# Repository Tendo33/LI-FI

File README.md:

# Li-Fi (Light Fidelity): Visible Light Communication Based on STM32

Innovative advancements in wireless communication have led to the development of Li-Fi, a technology that harnesses the power of visible light for data transmission. Li-Fi, or Light Fidelity, is a form of visible light communication (VLC) that uses light-emitting diodes (LEDs) as a medium for high-speed, bidirectional data transfer. This technology leverages the rapid switching capabilities of LEDs to transmit binary information, offering a new dimension to the realm of wireless networking.

At the heart of this cutting-edge system lies the STM32 microcontroller, a powerful and versatile device developed by STMicroelectronics. The STM32 family offers a wide range of performance, power consumption, and integration options, making it suitable for various applications, including complex high-end products and low-power devices. In the context of Li-Fi, the STM32 serves as the brain that controls the modulation and demodulation of light signals, enabling efficient and reliable data communication.

The STM32 microcontroller, with its robust processing capabilities, is capable of managing the intricate details of Li-Fi communication protocols. It can handle the modulation techniques required to encode digital data onto the light waves and decode them at the receiver end. Moreover, the STM32 can support additional functionalities such as error correction, signal processing, and security features, which are crucial for maintaining high data integrity and confidentiality in Li-Fi networks.

One of the significant advantages of using Li-Fi technology over traditional Wi-Fi is the potential for higher bandwidth and data rates. Since the visible light spectrum has a much wider bandwidth than radio frequencies, Li-Fi can theoretically achieve gigabit speeds. Additionally, Li-Fi can coexist harmoniously with existing wireless technologies without causing interference, making it a promising solution for densely populated areas or environments where radio frequency emissions are restricted, such as hospitals and aircraft cabins.

The integration of Li-Fi with the STM32 microcontroller opens up exciting possibilities for various industries. From enhancing the Internet of Things (IoT) ecosystem to improving connectivity in smart homes and offices, Li-Fi powered by STM32 can revolutionize the way we interact with our environment. With its ability to provide secure, high-speed connectivity using everyday lighting fixtures, Li-Fi stands as a beacon of innovation in the field of wireless communication.

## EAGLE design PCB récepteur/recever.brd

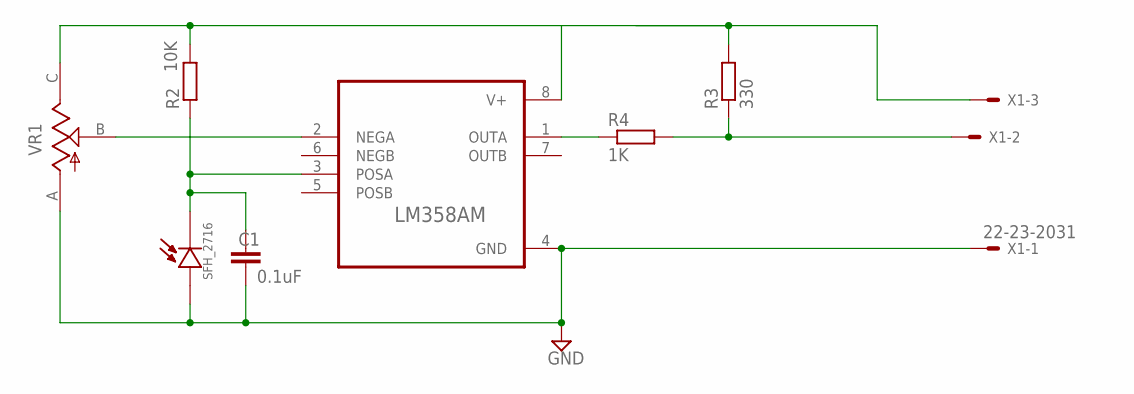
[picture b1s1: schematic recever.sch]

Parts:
C1: 0.1uF; C1206
D1: SFH_2716; LEDC2012X100N
R2: 10K; R1206
R3: 330; R1206
R4: 1K; R1206
U1: LM358AM; SOIC127P599X175-8N
VR1: 10K; TRIM_TS53YJ103MR10
X1: 22-23-2031

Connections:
GND: C1.2, D1.A, U1.4 (GND), VR1.A, X1.1
unnamed: R2.2, R3.2, U1.8 (V+), VR1.C, X1.3
unnamed: R3.1, R4.2, X1.2
unnamed: U1.2 (NEGA), VR1.B
unnamed: C1.1, D1.C, R2.1, U1.3 (POSA)
unnamed: R4.1, U1.1 (OUTA)

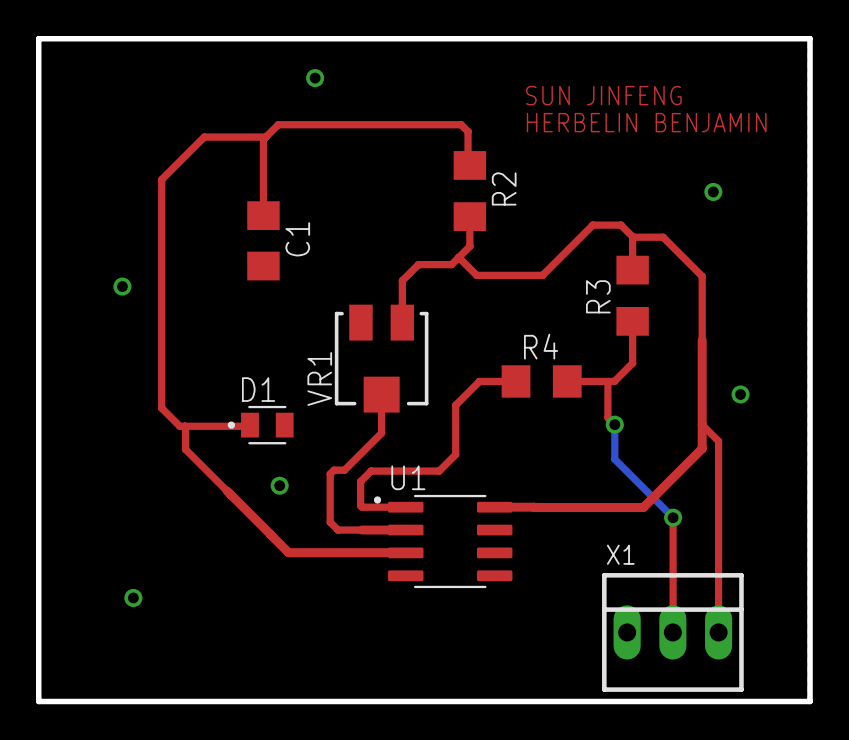
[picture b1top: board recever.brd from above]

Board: 2 copper layers, 42.9 x 36.8 mm, 8 parts (0 on the bottom side), 6 nets.

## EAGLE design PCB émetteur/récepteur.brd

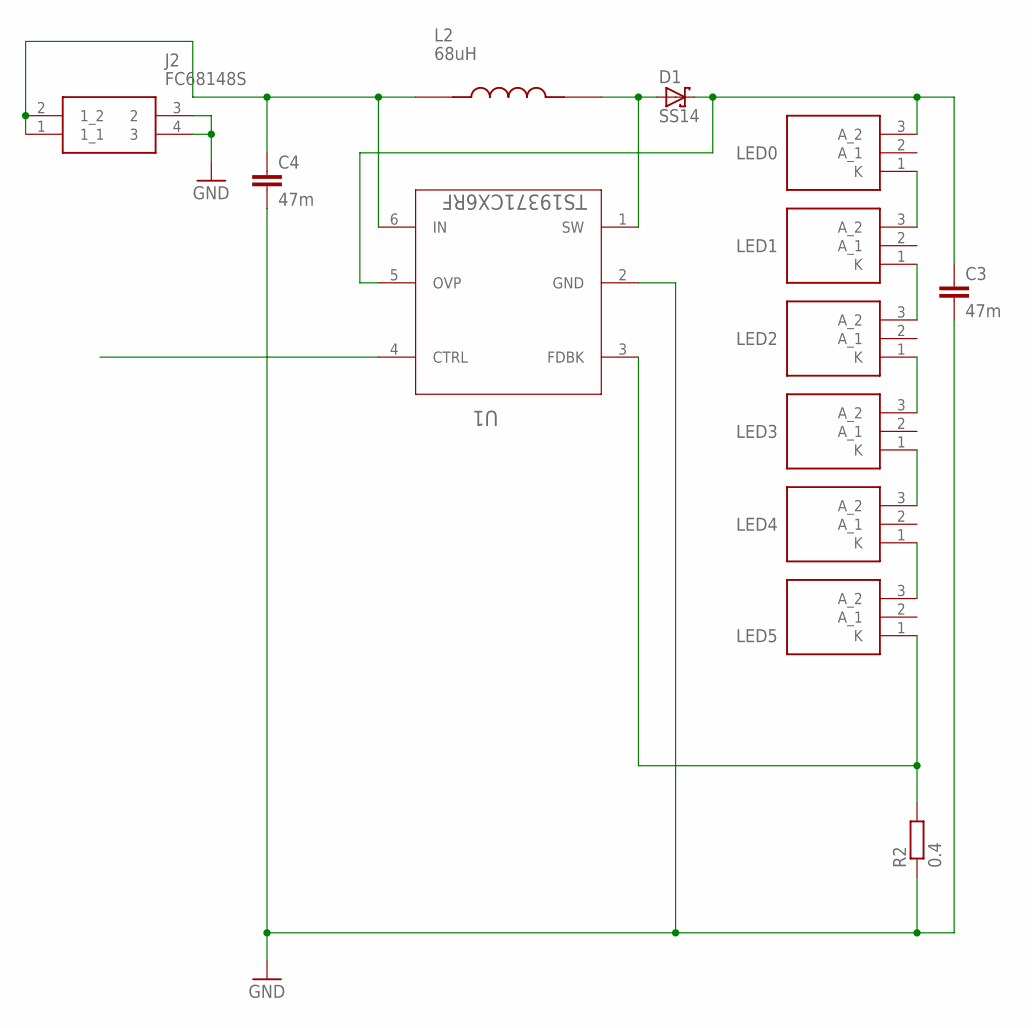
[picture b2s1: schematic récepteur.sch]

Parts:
C3, C4: 47m; C1206K
D1: SS14; DO-214AC
J2: FC68148S; FC68148S_2
L2: 68uH; IND_1255AY-680M=P3
LED0, LED1, LED2, LED3, LED4, LED5: LED-CREE-JK3030; JK3030AWT000000000A0HK230E
R2: 0.4; R1206
U1: TS19371CX6RF; SOT95P280X125-6N

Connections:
GND: C3.2, C4.2, J2.3 (2), J2.4 (3), R2.1, U1.2 (GND)
unnamed: LED0.1 (K), LED1.3 (A_2)
unnamed: LED1.1 (K), LED2.3 (A_2)
unnamed: LED2.1 (K), LED3.3 (A_2)
unnamed: LED3.1 (K), LED4.3 (A_2)
unnamed: LED4.1 (K), LED5.3 (A_2)
unnamed: LED5.1 (K), R2.2, U1.3 (FDBK)
unnamed: C4.1, J2.1 (1_1), J2.2 (1_2), L2.1, U1.6 (IN)
unnamed: D1.A, L2.2, U1.1 (SW)
unnamed: C3.1, D1.K, LED0.3 (A_2), U1.5 (OVP)

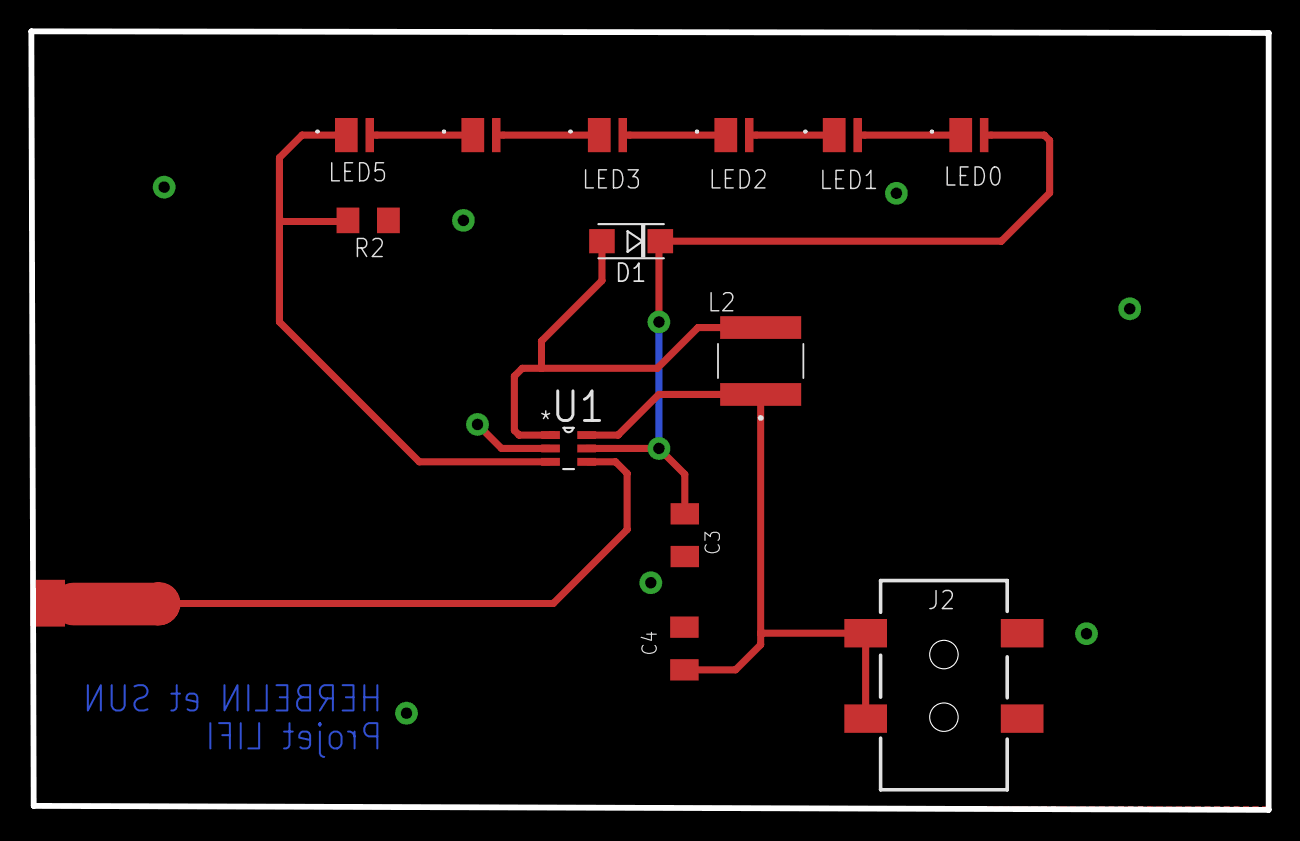
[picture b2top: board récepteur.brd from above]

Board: 2 copper layers, 87.0 x 54.7 mm, 13 parts (0 on the bottom side), 10 nets.
